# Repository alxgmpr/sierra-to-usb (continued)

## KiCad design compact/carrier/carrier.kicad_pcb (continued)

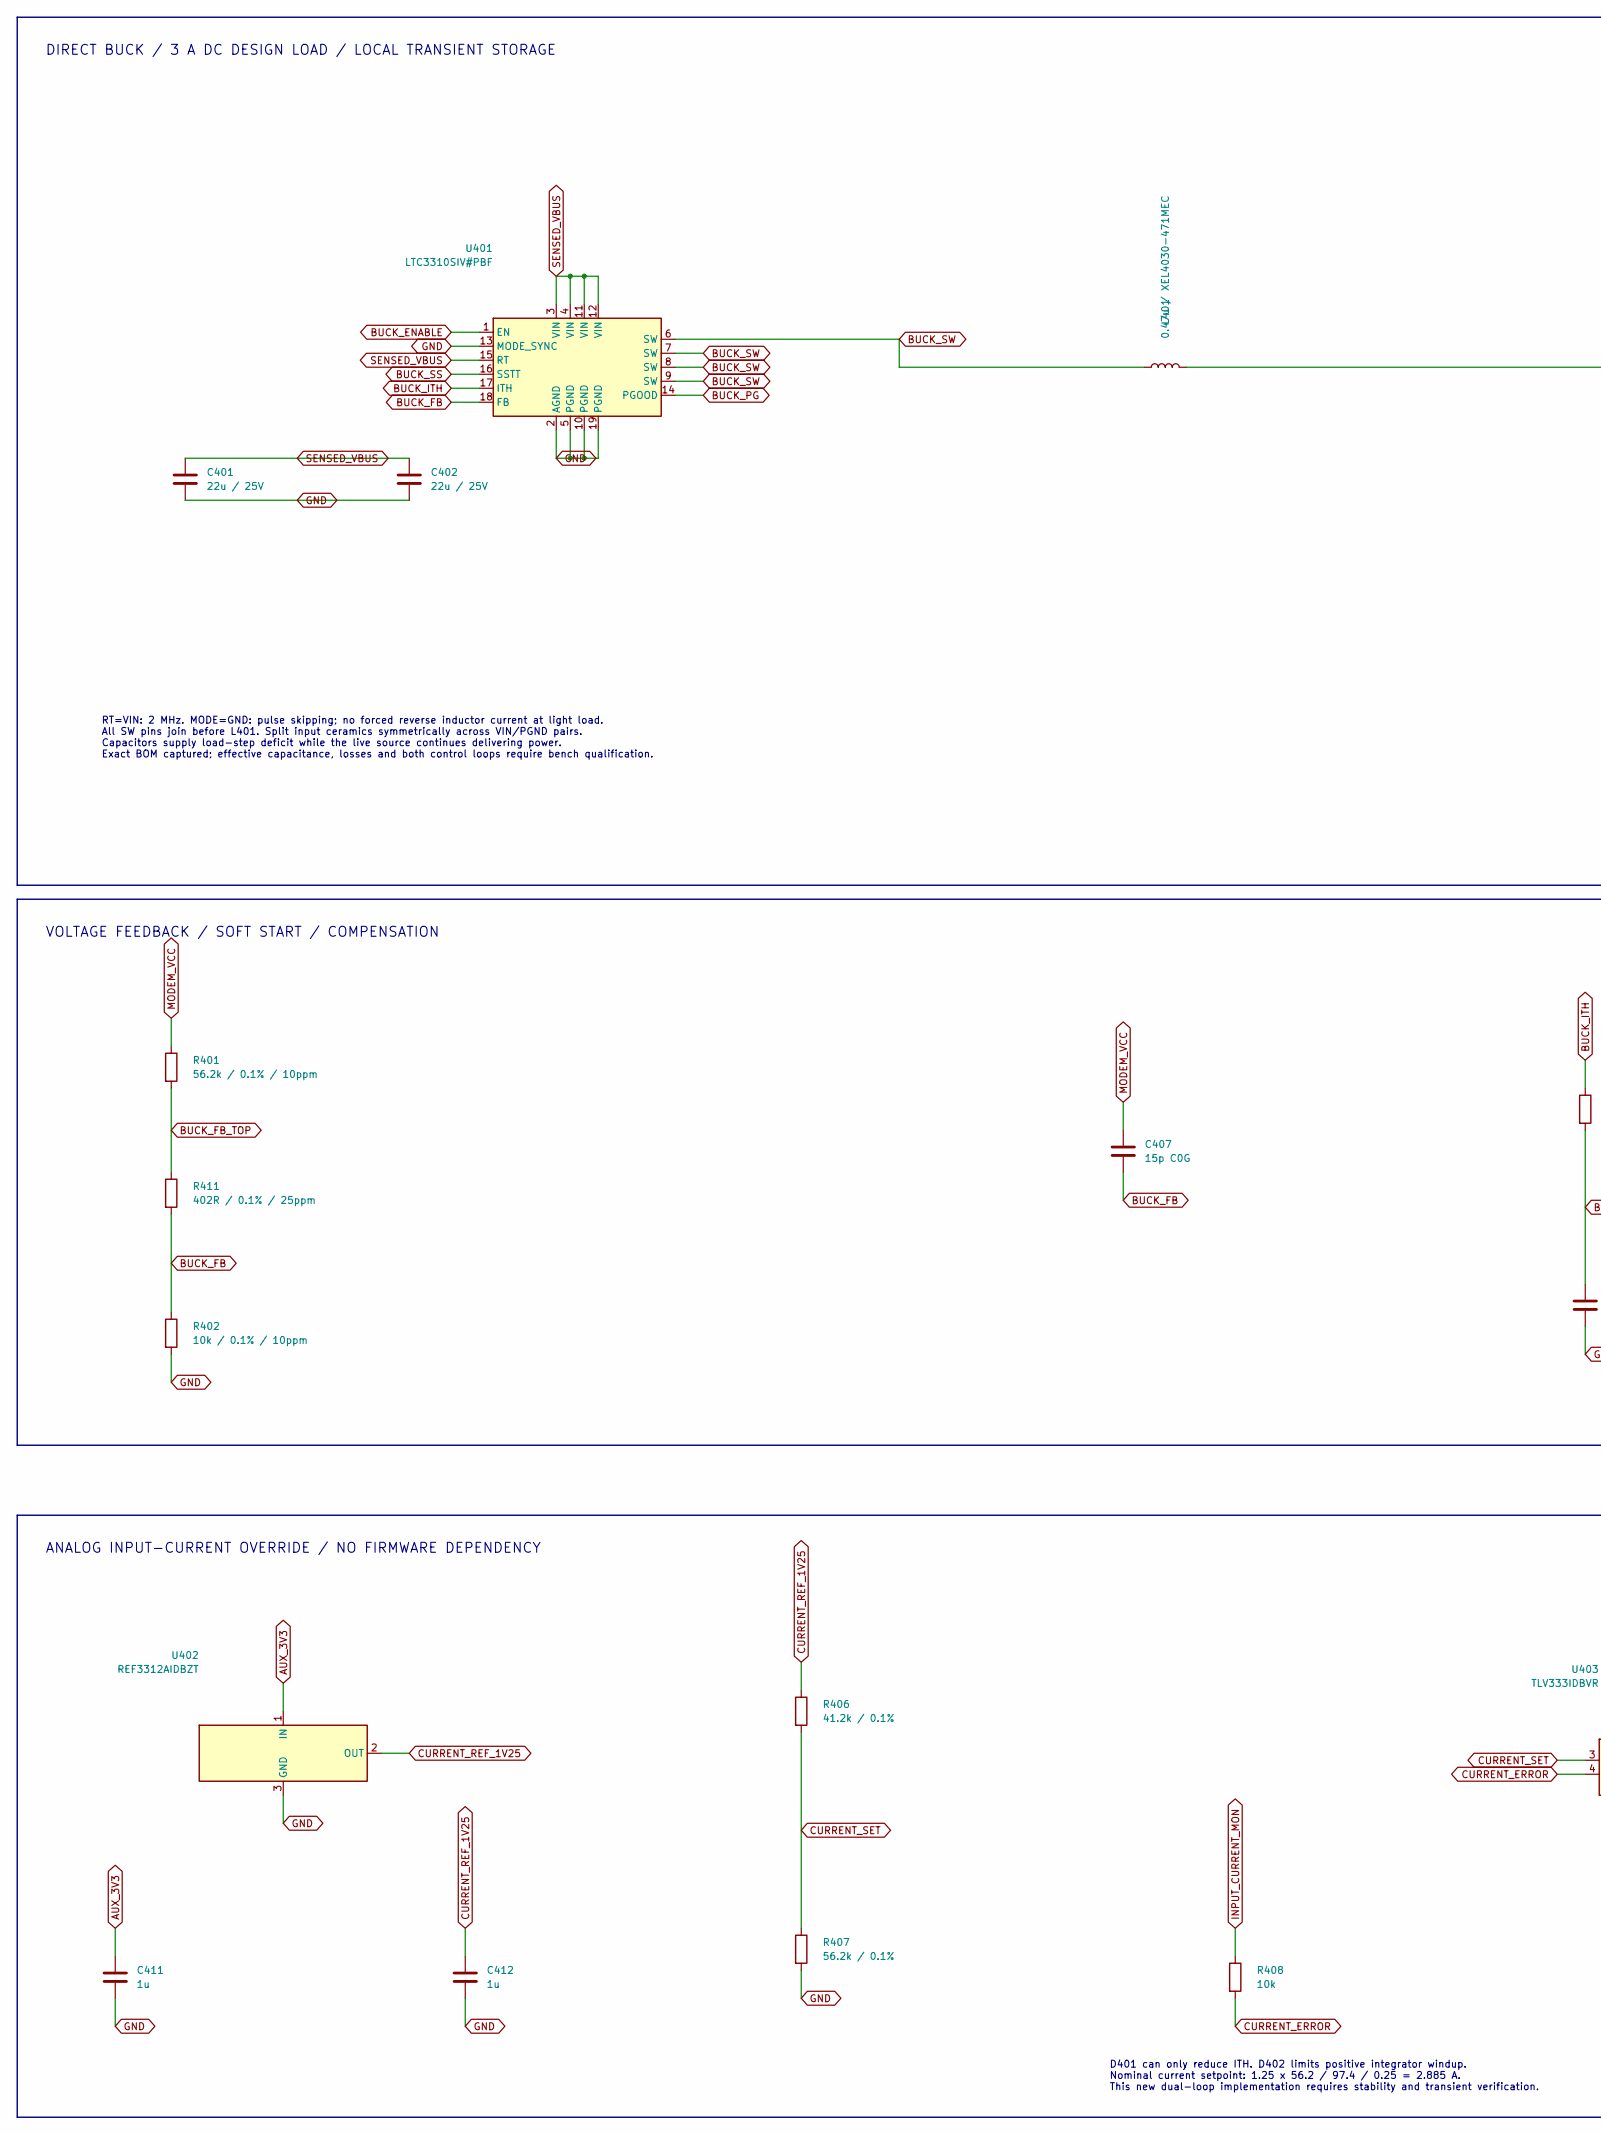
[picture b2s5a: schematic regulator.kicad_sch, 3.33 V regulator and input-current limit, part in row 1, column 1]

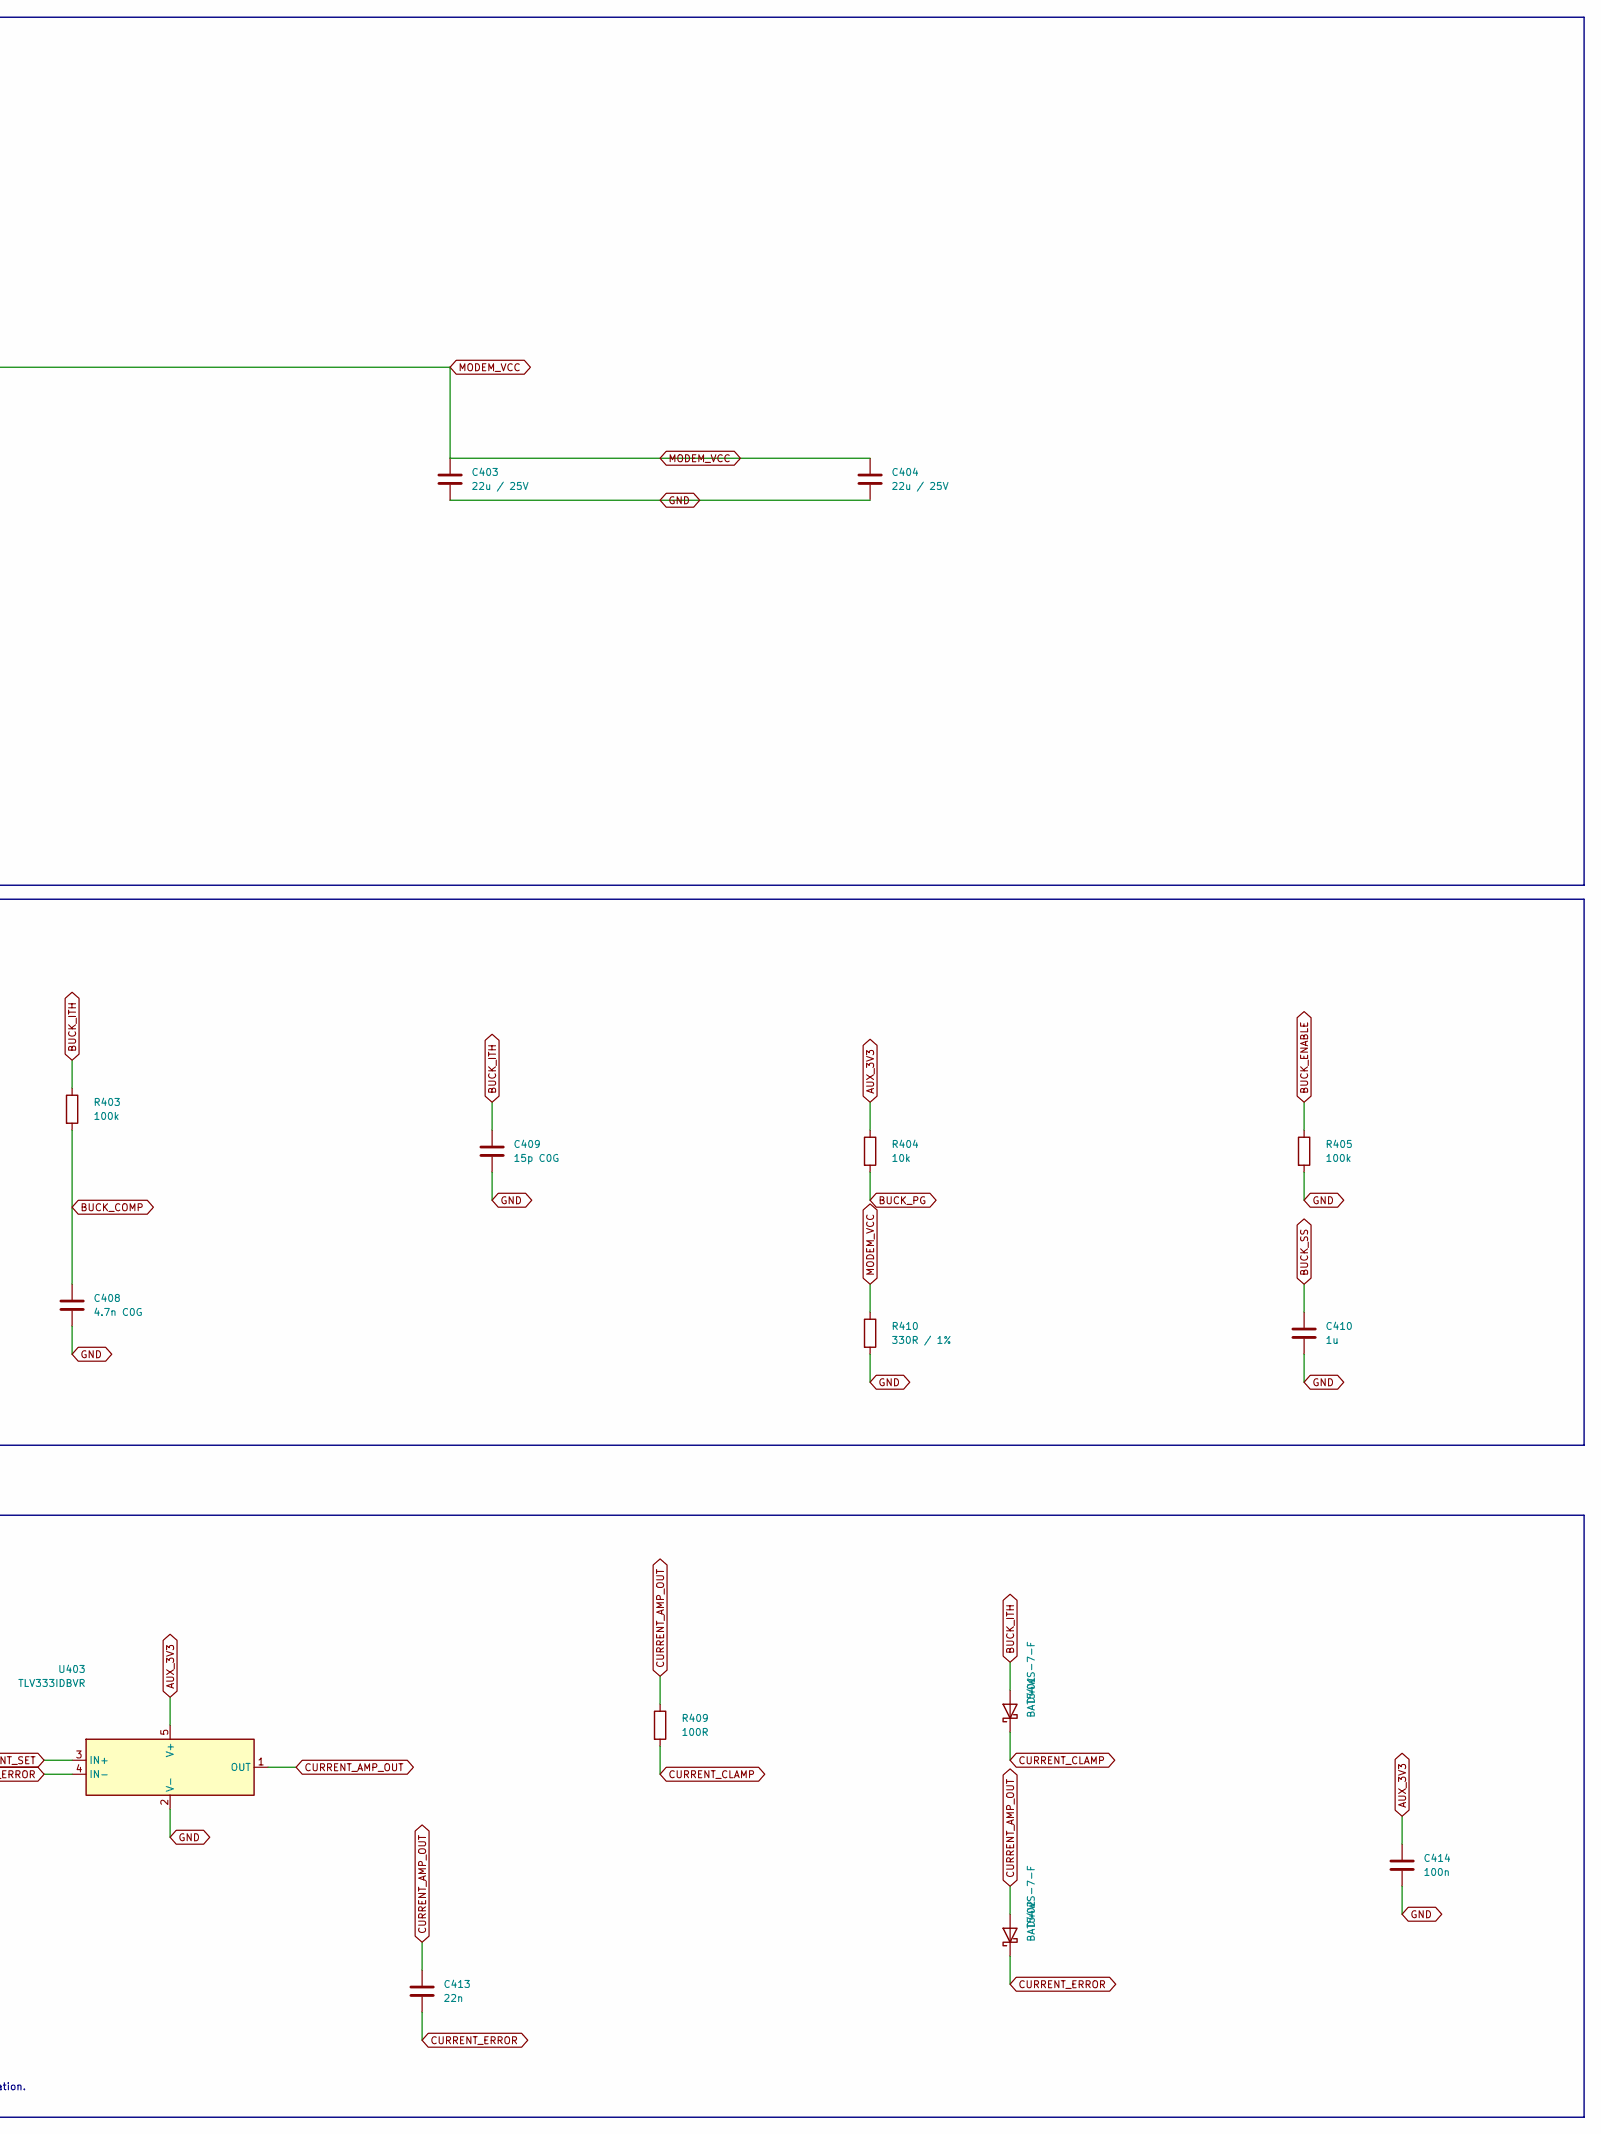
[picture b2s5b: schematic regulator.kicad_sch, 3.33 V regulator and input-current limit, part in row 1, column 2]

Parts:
C401, C402, C403, C404: 22u / 25V; C_1210_3225Metric; MPN C3225X7R1E226M250AB
C407, C409: 15p C0G; C_0805_2012Metric; MPN C0805C150J5GACTU
C408: 4.7n C0G; C_0805_2012Metric; MPN C2012C0G1H472J060AA
C410, C411, C412: 1u; C_1206_3216Metric; MPN C3216X7R1H105K160AB
C413: 22n; C_0805_2012Metric; MPN C0805C223J5GACTU
C414: 100n; C_0805_2012Metric; MPN C2012X7R1H104K085AA
D401, D402: BAT54WS-7-F; D_SOD-323; MPN BAT54WS-7-F
L401: 0.47u / XEL4030-471MEC; L_Coilcraft_XEL4030; MPN XEL4030-471MEC
R401: 56.2k / 0.1% / 10ppm; R_0603_1608Metric; MPN ERA-3ARB5622V
R402: 10k / 0.1% / 10ppm; R_0603_1608Metric; MPN ERA-3ARB103V
R403, R405: 100k; R_0603_1608Metric; MPN RC0603FR-07100KL
R404, R408: 10k; R_0603_1608Metric; MPN RC0603FR-0710KL
R406: 41.2k / 0.1%; R_0603_1608Metric; MPN RT0603BRD0741K2L
R407: 56.2k / 0.1%; R_0603_1608Metric; MPN RT0603BRD0756K2L
R409: 100R; R_0603_1608Metric; MPN RC0603FR-07100RL
R410: 330R / 1%; R_1206_3216Metric; MPN RC1206FR-07330RL
R411: 402R / 0.1% / 25ppm; R_0603_1608Metric; MPN RT0603BRD07402RL
U401: LTC3310SIV#PBF; LTC_LQFN18_3x3_05-08-1548; MPN LTC3310SIV#PBF
U402: REF3312AIDBZT; SOT-23; MPN REF3312AIDBZT
U403: TLV333IDBVR; SOT-23-5; MPN TLV333IDBVR

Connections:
AUX_3V3: C411.1, C414.1, R404.1, U402.1 (IN), U403.5 (V+); also elsewhere on the board
BUCK_COMP: C408.1, R403.2
BUCK_ENABLE: R405.1, U401.1 (EN); also elsewhere on the board
BUCK_FB: C407.2, R402.1, R411.2, U401.18 (FB)
BUCK_FB_TOP: R401.2, R411.1
BUCK_ITH: C409.1, D401.2 (A), R403.1, U401.17 (ITH); also elsewhere on the board
BUCK_PG: R404.2, U401.14 (PGOOD)
BUCK_SS: C410.1, U401.16 (SSTT)
BUCK_SW: L401.1, U401.6 (SW), U401.7 (SW), U401.8 (SW), U401.9 (SW)
CURRENT_AMP_OUT: C413.1, D402.2 (A), R409.1, U403.1 (OUT)
CURRENT_CLAMP: D401.1 (K), R409.2
CURRENT_ERROR: C413.2, D402.1 (K), R408.2, U403.4 (IN-)
CURRENT_REF_1V25: C412.1, R406.1, U402.2 (OUT)
CURRENT_SET: R406.2, R407.1, U403.3 (IN+)
GND: C401.2, C402.2, C403.2, C404.2, C408.2, C409.2, C410.2, C411.2, C412.2, C414.2, R402.2, R405.2, R407.2, R410.2, U401.2 (AGND), U401.5 (PGND), U401.10 (PGND), U401.13 (MODE_SYNC), U401.19 (PGND), U402.3 (GND), U403.2 (V-); also elsewhere on the board
INPUT_CURRENT_MON: R408.1; also elsewhere on the board
MODEM_VCC: C403.1, C404.1, C407.1, L401.2, R401.1, R410.1; also elsewhere on the board
SENSED_VBUS: C401.1, C402.1, U401.3 (VIN), U401.4 (VIN), U401.11 (VIN), U401.12 (VIN), U401.15 (RT); also elsewhere on the board

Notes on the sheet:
DIRECT BUCK / 3 A DC DESIGN LOAD / LOCAL TRANSIENT STORAGE
RT=VIN: 2 MHz. MODE=GND: pulse skipping; no forced reverse inductor current at light load. All SW pins join before L401. Split input ceramics symmetrically across VIN/PGND pairs. Capacitors supply load-step deficit while the live source continues delivering power. Exact BOM captured; effective capa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
VOLTAGE FEEDBACK / SOFT START / COMPENSATION
ANALOG INPUT-CURRENT OVERRIDE / NO FIRMWARE DEPENDENCY
D401 can only reduce ITH. D402 limits positive integrator windup. Nominal current setpoint: 1.25 x 56.2 / 97.4 / 0.25 = 2.885 A. This new dual-loop implementation requires stability and transient verification.

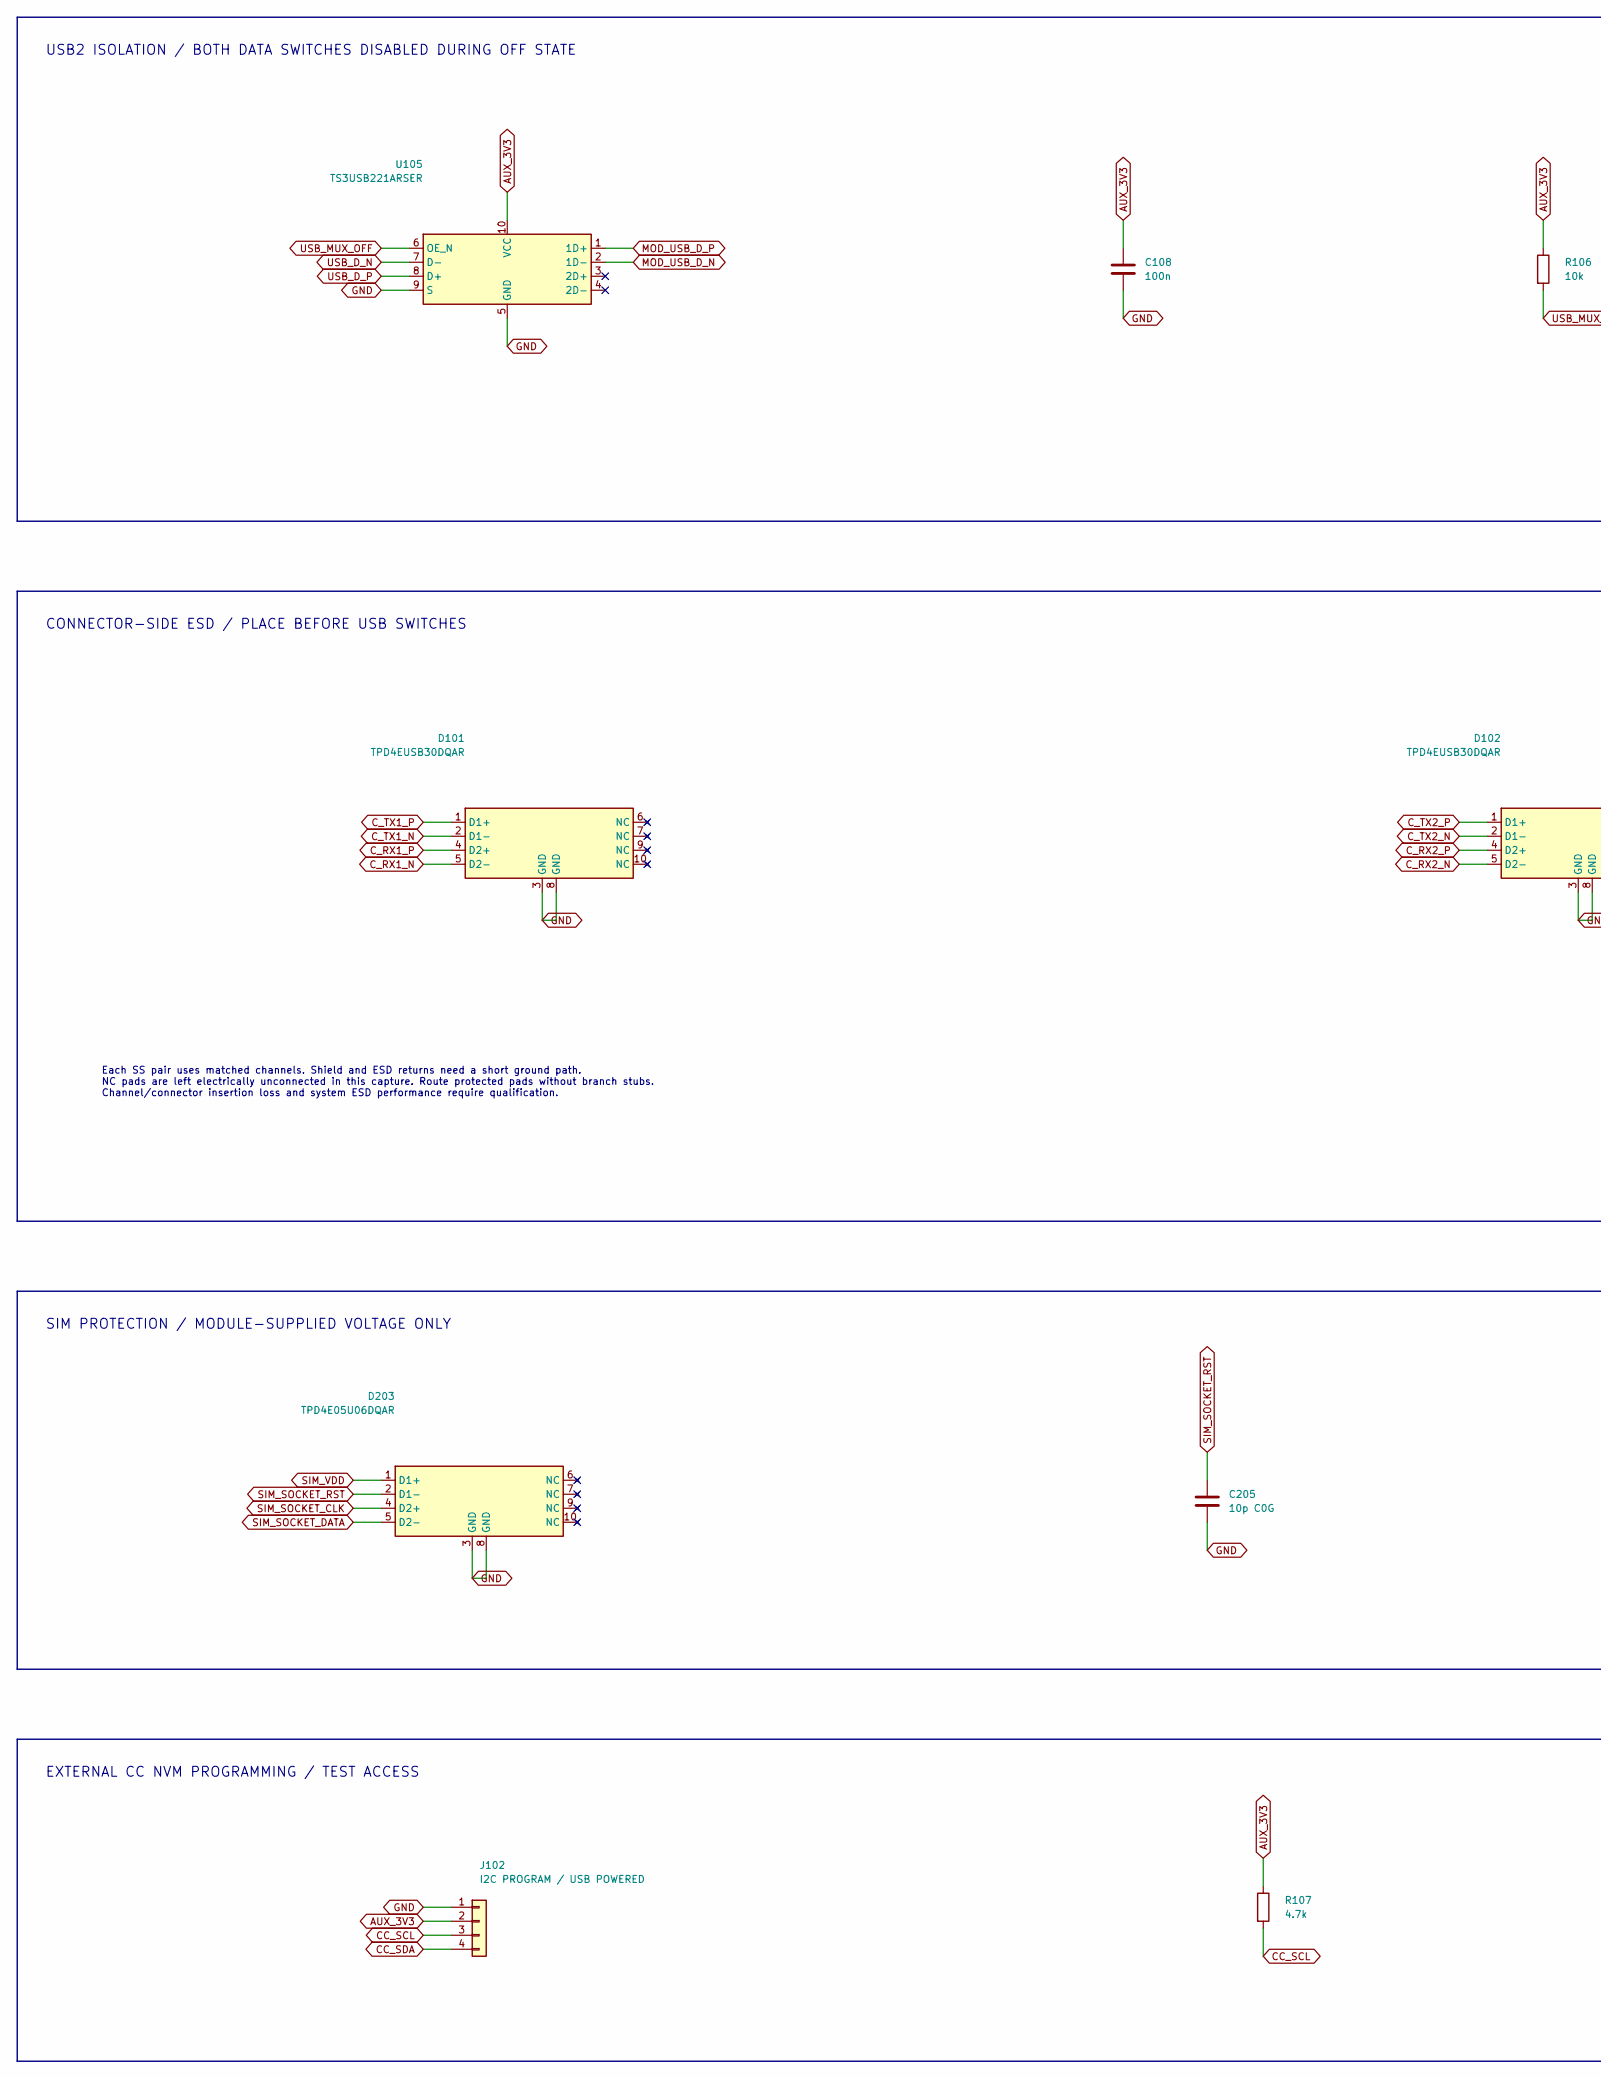
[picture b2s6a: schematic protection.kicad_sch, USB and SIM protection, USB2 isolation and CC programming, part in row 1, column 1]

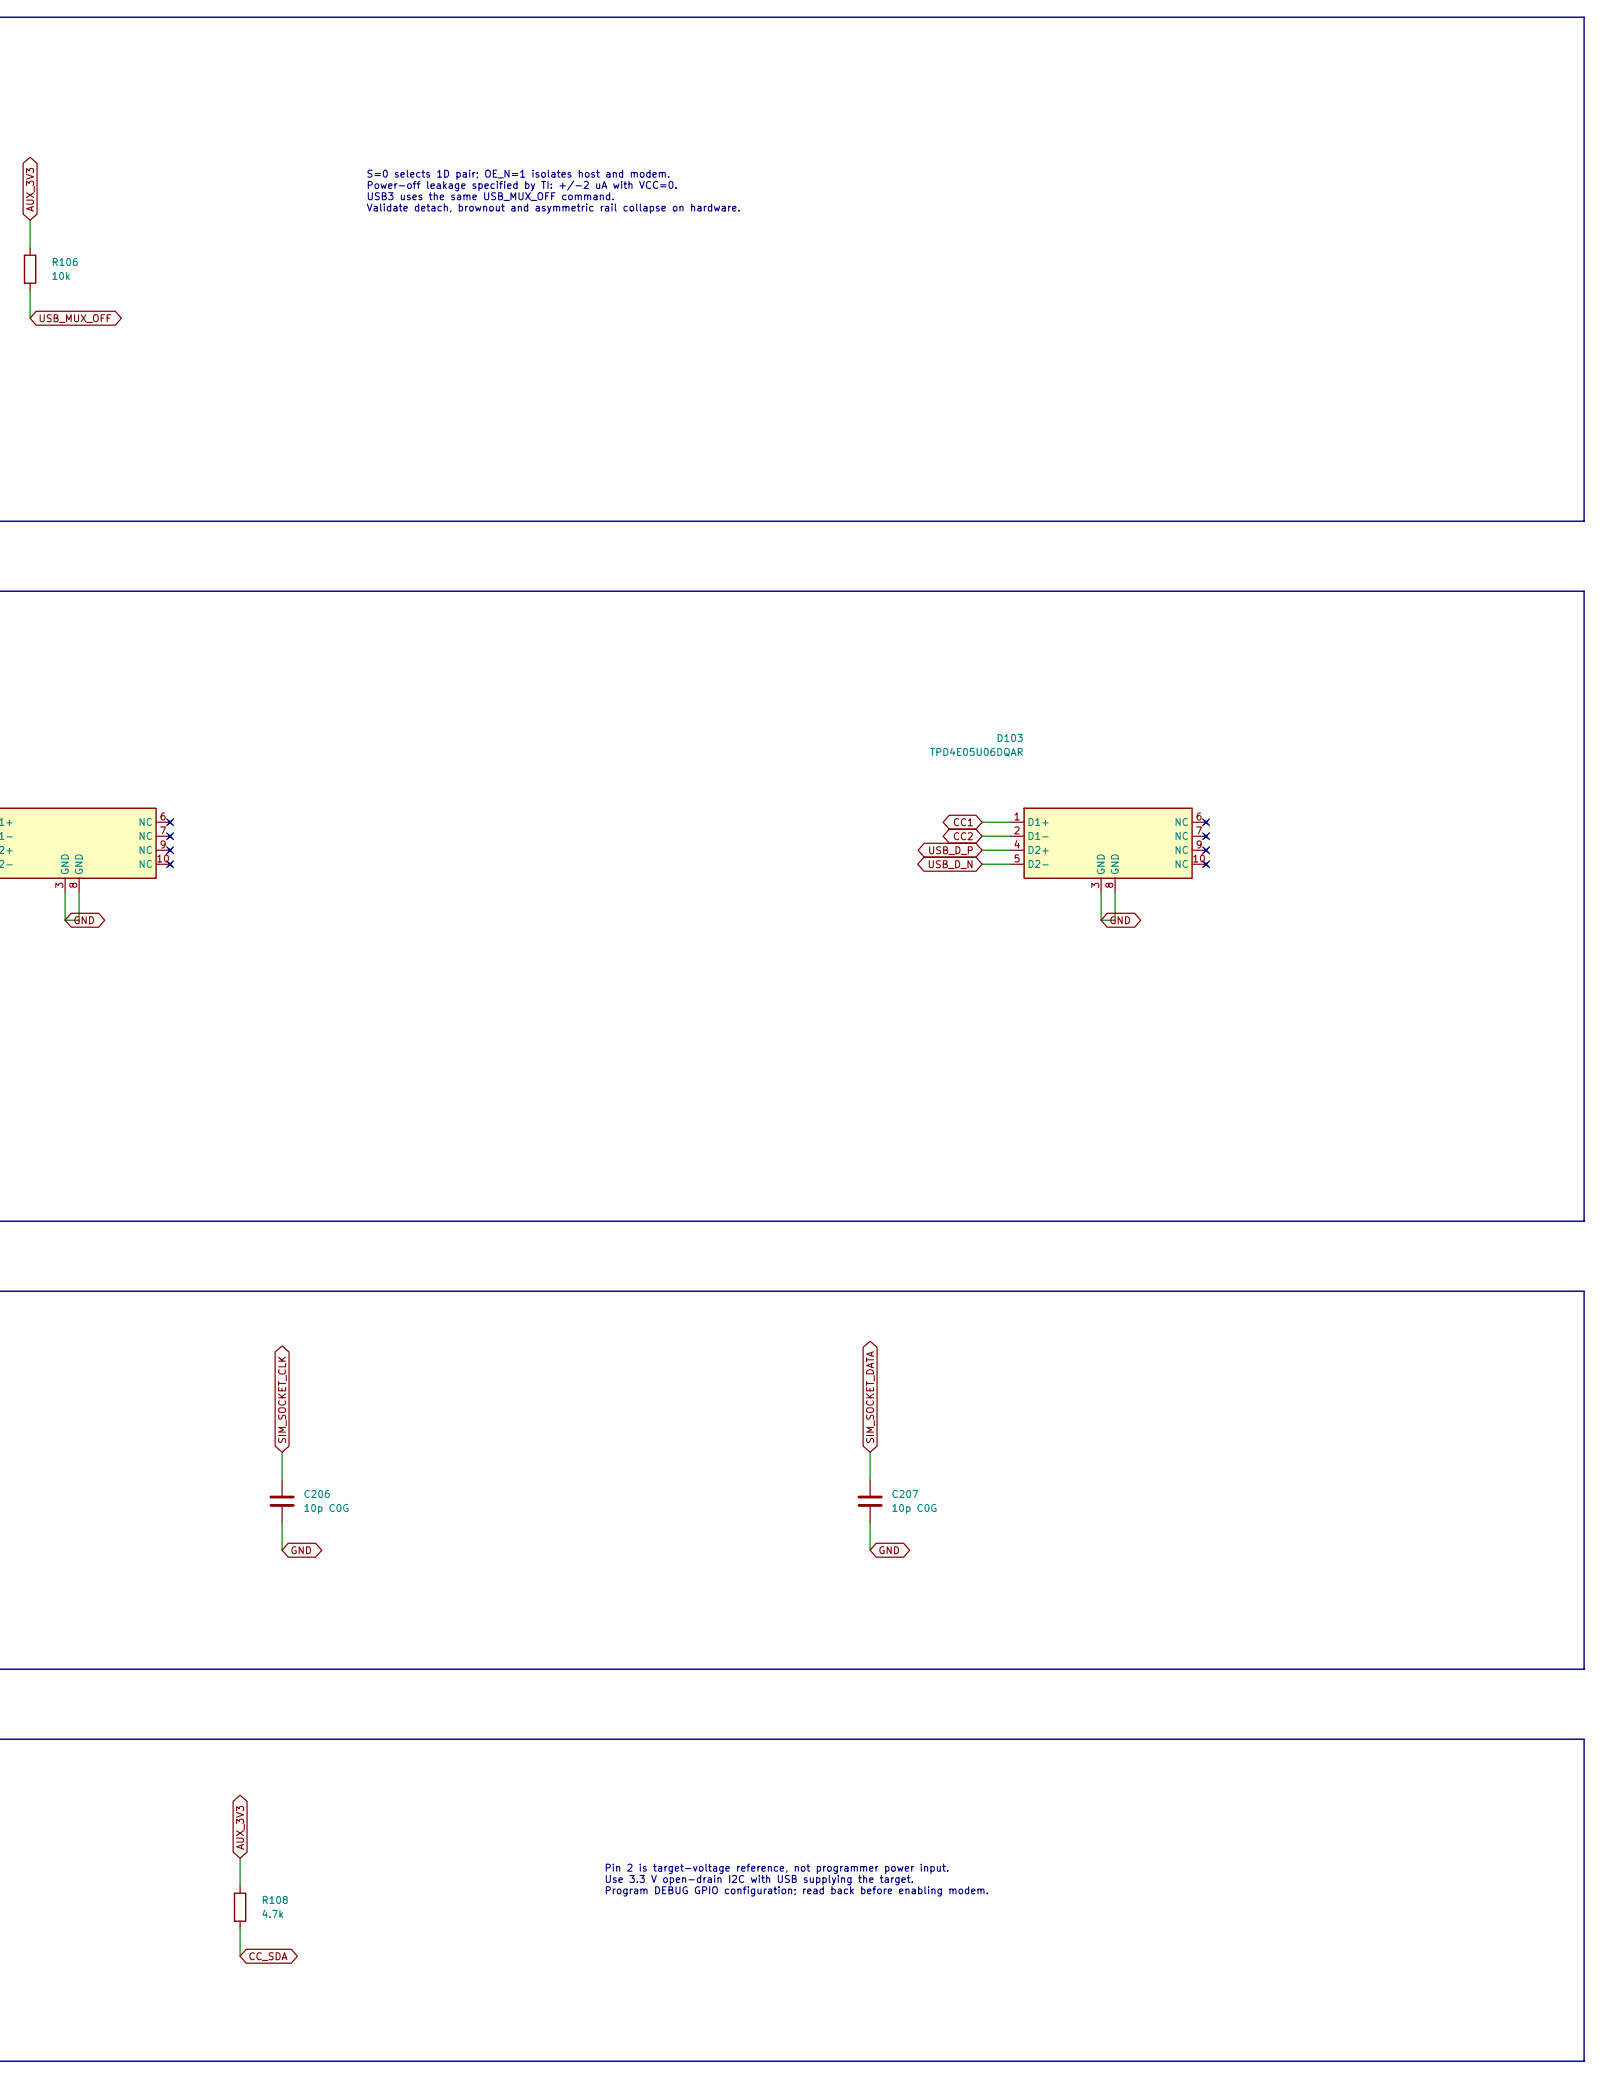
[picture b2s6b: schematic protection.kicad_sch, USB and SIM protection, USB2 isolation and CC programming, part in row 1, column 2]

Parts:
C108: 100n; C_0805_2012Metric; MPN C2012X7R1H104K085AA
C205, C206, C207: 10p C0G; C_0805_2012Metric; MPN C0805C100J5GACTU
D101, D102: TPD4EUSB30DQAR; USON-10_2.5x1.0mm_P0.5mm; MPN TPD4EUSB30DQAR
D103, D203: TPD4E05U06DQAR; USON-10_2.5x1.0mm_P0.5mm; MPN TPD4E05U06DQAR
J102: I2C PROGRAM / USB POWERED; PinHeader_1x04_P2.54mm_Vertical; MPN TSW-104-07-G-S
R106: 10k; R_0603_1608Metric; MPN RC0603FR-0710KL
R107, R108: 4.7k; R_0603_1608Metric; MPN RC0603FR-074K7L
U105: TS3USB221ARSER; Texas_UQFN-10_1.5x2mm_P0.5mm; MPN TS3USB221ARSER

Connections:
AUX_3V3: C108.1, J102.2, R106.1, R107.1, R108.1, U105.10 (VCC); also elsewhere on the board
CC1: D103.1 (D1+); also elsewhere on the board
CC2: D103.2 (D1-); also elsewhere on the board
CC_SCL: J102.3, R107.2; also elsewhere on the board
CC_SDA: J102.4, R108.2; also elsewhere on the board
C_RX1_N: D101.5 (D2-); also elsewhere on the board
C_RX1_P: D101.4 (D2+); also elsewhere on the board
C_RX2_N: D102.5 (D2-); also elsewhere on the board
C_RX2_P: D102.4 (D2+); also elsewhere on the board
C_TX1_N: D101.2 (D1-); also elsewhere on the board
C_TX1_P: D101.1 (D1+); also elsewhere on the board
C_TX2_N: D102.2 (D1-); also elsewhere on the board
C_TX2_P: D102.1 (D1+); also elsewhere on the board
GND: C108.2, C205.2, C206.2, C207.2, D101.3 (GND), D101.8 (GND), D102.3 (GND), D102.8 (GND), D103.3 (GND), D103.8 (GND), D203.3 (GND), D203.8 (GND), J102.1, U105.5 (GND), U105.9 (S); also elsewhere on the board
MOD_USB_D_N: U105.2 (1D-); also elsewhere on the board
MOD_USB_D_P: U105.1 (1D+); also elsewhere on the board
SIM_SOCKET_CLK: C206.1, D203.4 (D2+); also elsewhere on the board
SIM_SOCKET_DATA: C207.1, D203.5 (D2-); also elsewhere on the board
SIM_SOCKET_RST: C205.1, D203.2 (D1-); also elsewhere on the board
SIM_VDD: D203.1 (D1+); also elsewhere on the board
USB_D_N: D103.5 (D2-), U105.7 (D-); also elsewhere on the board
USB_D_P: D103.4 (D2+), U105.8 (D+); also elsewhere on the board
USB_MUX_OFF: R106.2, U105.6 (OE_N); also elsewhere on the board

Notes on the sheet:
USB2 ISOLATION / BOTH DATA SWITCHES DISABLED DURING OFF STATE
S=0 selects 1D pair; OE_N=1 isolates host and modem. Power-off leakage specified by TI: +/-2 uA with VCC=0. USB3 uses the same USB_MUX_OFF command. Validate detach, brownout and asymmetric rail collapse on hardware.
CONNECTOR-SIDE ESD / PLACE BEFORE USB SWITCHES
Each SS pair uses matched channels. Shield and ESD returns need a short ground path. NC pads are left electrically unconnected in this capture. Route protected pads without branch stubs. Channel/connector insertion loss and system ESD performance require qualification.
SIM PROTECTION / MODULE-SUPPLIED VOLTAGE ONLY
EXTERNAL CC NVM PROGRAMMING / TEST ACCESS
Pin 2 is target-voltage reference, not programmer power input. Use 3.3 V open-drain I2C with USB supplying the target. Program DEBUG GPIO configuration; read back before enabling modem.
